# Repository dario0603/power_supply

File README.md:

<p align="left">

</p>

# Linear Power Supply Project

Progetto universitario per la realizzazione e simulazione di un **Alimentatore da Banco Stabilizzato** , completo di schemi elettrici KiCad, simulazioni LTspice, documentazione tecnica e file Gerber per la produzione del PCB.

---

## Panoramica del Progetto

Il progetto riguarda lo studio, la modellizzazione e la progettazione hardware di un alimentatore stabilizzato.

## 1. Obiettivi del Progetto
Il progetto illustra la progettazione di un alimentatore da banco stabilizzato con le seguenti caratteristiche principali:
*   **Tensione di uscita regolabile:** da $0V$ a $20V$ (continua).
*   **Corrente di uscita limitabile e regolabile:** da $0A$ a $5A$.
*   **Modalità Tracking:** permette di erogare in uscita una tensione pari a quella applicata su appositi pin esterni (utile per generare tensioni duali).
*   **Monitoraggio:** Misura in tempo reale di tensione e corrente con visualizzazione a schermo.

## 2. Architettura del Circuito di Potenza
L'alimentatore è strutturato in blocchi funzionali classici:
*   **Trasformatore:** Abbassa la tensione di rete (230V, 50Hz) a un valore di $25V$ efficaci sul secondario.
*   **Raddrizzatore:** È stato scelto un **raddrizzatore a doppia semi-onda** (ponte di diodi) poiché garantisce un fattore di forma migliore e richiede un condensatore di filtro di capacità dimezzata rispetto alla singola semi-onda ($C \approx 14286 \mu F$ per un ripple di $3,5V$).
*   **Filtro Capacitivo:** Livella la tensione raddrizzata riducendo la tensione di ripple.
*   **Regolatore Lineare:** Prende in ingresso la tensione filtrata e la stabilizza al valore desiderato tramite un amplificatore di errore e un transistor di passo.

## 3. Circuito Regolatore e Limitazione di Corrente
Le scelte progettuali più rilevanti per la regolazione e la protezione includono:
*   **Integrato LM723:** Utilizzato come base per il circuito di regolazione della tensione.
*   **Transistor di Potenza (Pass Transistors):** Viene utilizzata una configurazione Darlington per garantire un guadagno di corrente ($\beta_f$) sufficiente. Sono impiegati più transistor di potenza (TIP3055 o 2N3055) **collegati in parallelo** per dividere il carico di corrente.
    *   *Problema critico risolto:* Per evitare il "run-down termico" (squilibrio di corrente dovuto alle variazioni di $\beta_f$ con la temperatura), sono state inserite piccole resistenze di emettitore in serie ai BJT.
*   **Limitatore di Corrente:** Sfrutta una resistenza di shunt ($R_{sh} = 0,2 \Omega$) in serie al carico. La caduta di tensione ai suoi capi è letta da un amplificatore differenziale e confrontata (comparatore) con una tensione di riferimento ($V_{zi}$). Se la corrente supera la soglia, un transistor devia la corrente di base del BJT di passo, limitando l'uscita.

## 4. Alimentazioni Ausiliarie
Per il corretto funzionamento degli amplificatori operazionali (TL082) e della logica di controllo, il circuito ricava tensioni di servizio secondarie:
*   $\pm12V$ stabilizzate (utilizzando LM7812 e LM7912).
*   $+5V$ stabilizzati (tramite LM7805).
*   Tensioni negative specifiche create con diodi Zener per rispettare i limiti di alimentazione degli op-amp nella sezione di tracking in particolare una linea a $-3.8V$.

## 5. Circuiti di Misura (Voltmetro e Amperometro)
Per fornire misurazioni precise all'ADC del microcontrollore (fondo-scala $5V$):
*   **Voltmetro a Guadagno Variabile:** Utilizza un amplificatore non invertente dove il guadagno viene modificato selezionando resistenze di retroazione diverse tramite switch C-MOS analogici (74HC4066). Gestisce fondo-scala di $2V, 10V, 25V, 100V$.
*   **Amperometro con Resistore di Shunt:** Amplifica il segnale prelevato dalla stessa resistenza di shunt della limitazione. Anche qui si usano guadagni variabili per fondo-scala di $200mA, 1A, 2.5A, 8A$.

## 6. Integrità del Segnale e Analisi Termica
*   **Signal Integrity:** È stata calcolata l'induttanza, la capacità e la resistenza parassita delle piste del PCB più critiche. Le simulazioni sul "ringing" hanno confermato che con tempi di salita/discesa $> 5ns$, l'overshoot è trascurabile (sotto il 5%).
*   **Analisi Termica:** Essenziale per i dispositivi di potenza. Analizzando le curve di derating, è stato calcolato il valore di resistenza termica del dissipatore ($R_{thda}$) per i transistor e per il ponte di diodi, evidenziando la necessità (nel caso del TIP3055) di usare la pasta termica e l'eventuale ventilazione forzata per mantenere i componenti sotto le temperature critiche di $125^\circ C / 150^\circ C$.
*   **FMEA (Failure Mode and Effects Analysis):** La relazione contiene tabelle dettagliate per valutare Gravità (S), Occorrenza (O) e Rilevabilità (D) in caso di guasti a condensatori o componenti chiave, calcolando l'indice di rischio globale (RPN).

---

## Simulazioni LTspice

All'interno della directory `Alimentatore taratura manuale/LTspice/` sono presenti due modelli di simulazione (da `v1.0` a `v2.0`):
contenenti varie analisi.

**Analisi di Ripple e Filtraggio**

**Risposta al gradino ($V_{\text{ref}}$)**

**Risposta alla rampa ($V_{\text{ref}}$)**

---

## Progettazione Hardware (KiCad)

I file di progetto PCB e schematici sono realizzati con **KiCad**.

**BOM Interattiva**: Disponibile all'interno delle cartelle KiCad sotto forma di `ibom.html` per facilitare l'assemblaggio dei componenti.

---

## Documentazione e Relazione

Per un'analisi approfondita dei calcoli teorici, delle scelte progettuali e delle prestazioni misurate, fare riferimento alla relazione completa presente nella repository:

* [Relazione Costruzioni (PDF)](Relazione/Relazione%20Costruzioni.pdf)

---

## Struttura della Repository

```text
.
├── Relazione/                        # Documentazione e report tecnico
│   ├── Relazione Costruzioni.pdf     # Documento finale in formato PDF
│   ├── Immagini/                     # Schemi, grafici e diagrammi usati nella relazione
│   └── Simulazioni/                  # File di simulazione generali LTspice
│
├── Alimentatore taratura manuale     # Schemi KiCad e simulazioni LTspice
│   ├── LtSpice
│   └── KiCad      
└── Controllore taratura manuale      # Schemi del controllore manuale

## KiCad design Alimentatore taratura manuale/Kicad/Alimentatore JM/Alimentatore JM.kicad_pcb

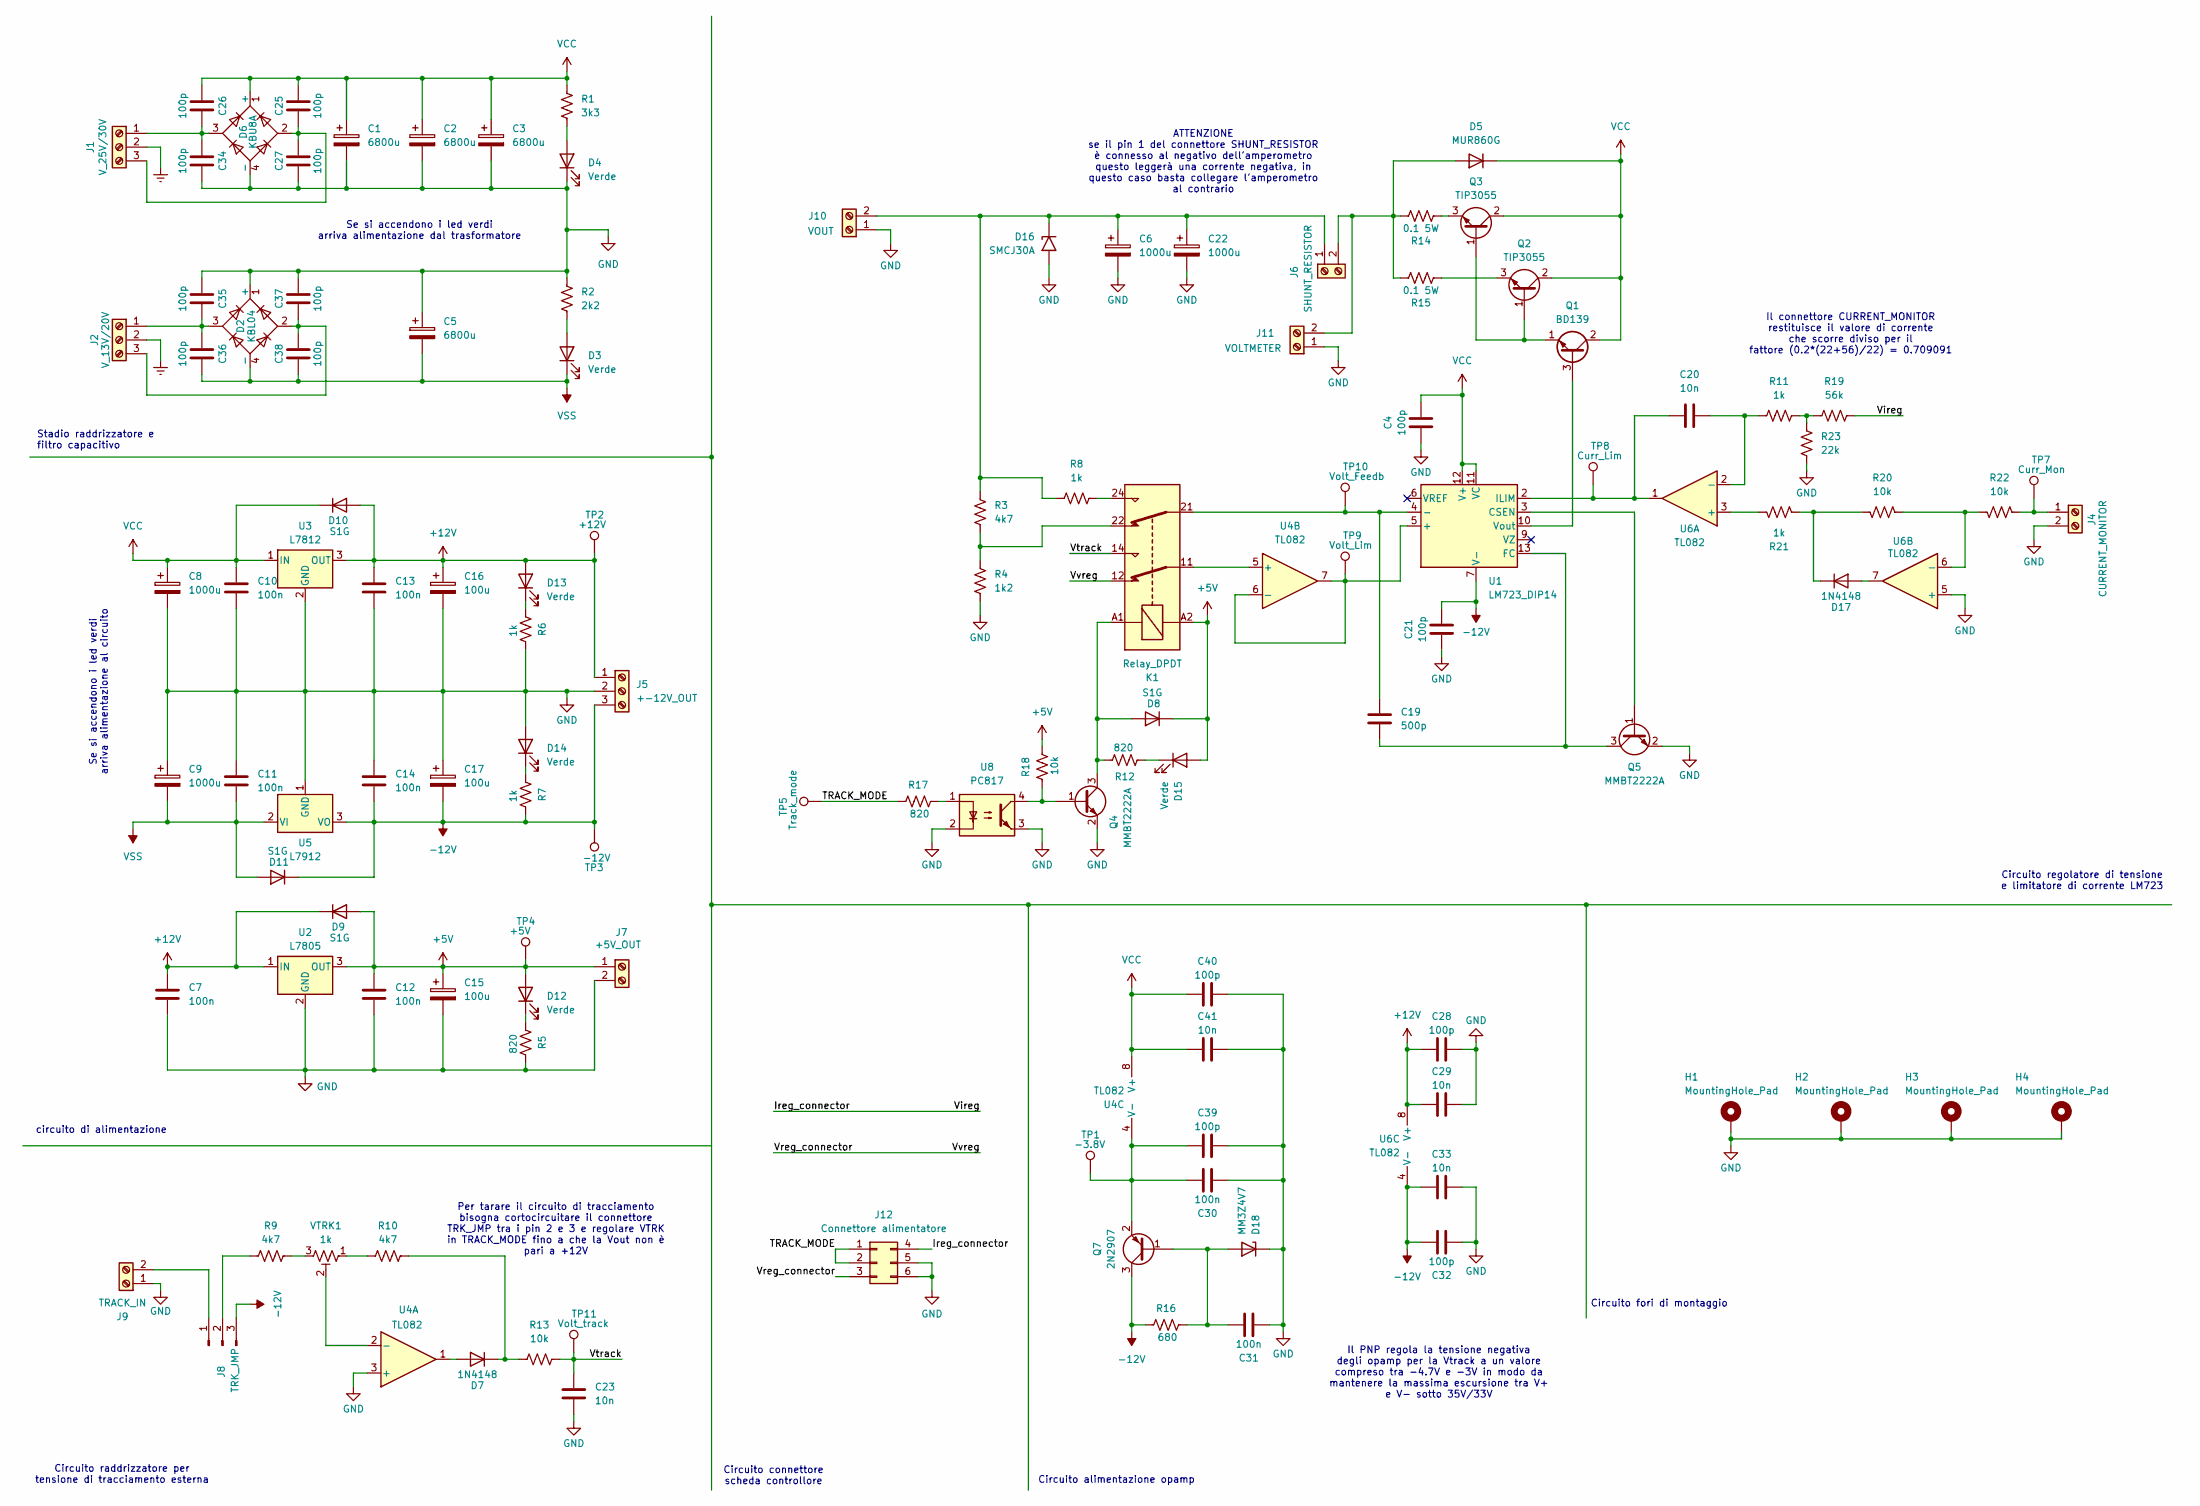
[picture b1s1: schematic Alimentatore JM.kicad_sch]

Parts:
C1, C2, C3, C5: 6800u; CP_Radial_D18.0mm_P7.50mm
C4, C21, C25, C26, C27, C28, C32, C34, C35, C36, C37, C38, C39, C40: 100p; C_0805_2012Metric_Pad1.18x1.45mm_HandSolder
C6, C8, C9, C22: 1000u; CP_Elec_8x10.5
C7, C10, C11, C12, C13, C14, C30, C31: 100n; C_0805_2012Metric_Pad1.18x1.45mm_HandSolder
C15, C16, C17: 100u; CP_Elec_8x10.5
C19: 500p; C_0805_2012Metric_Pad1.18x1.45mm_HandSolder
C20, C23, C29, C33, C41: 10n; C_0805_2012Metric_Pad1.18x1.45mm_HandSolder
D2: KBL04; Diode_Bridge_Vishay_KBL
D3, D4, D12, D13, D14, D15: Verde; LED_0805_2012Metric_Pad1.15x1.40mm_HandSolder
D5: MUR860G; TO-220-2_Vertical
D6: KBU8A; Diode_Bridge_Vishay_KBU
D7, D17: 1N4148; D_SOD-323F
D8, D9, D10, D11: S1G; D_SMA_Handsoldering
D16: SMCJ30A; D_SMC_Handsoldering
D18: MM3Z4V7; D_DO-35_SOD27_P7.62mm_Horizontal
H1, H2, H3, H4: MountingHole_Pad; MountingHole_3.2mm_M3_DIN965_Pad
J1: V_25V/30V; TerminalBlock_Phoenix_MKDS-1,5-3-5.08_1x03_P5.08mm_Horizont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
J2: V_13V/20V; TerminalBlock_Phoenix_MKDS-1,5-3-5.08_1x03_P5.08mm_Horizont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
J4: CURRENT_MONITOR; TerminalBlock_Phoenix_MKDS-1,5-2-5.08_1x02_P5.08mm_Horizont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
J5: +-12V_OUT; TerminalBlock_Phoenix_MKDS-1,5-3-5.08_1x03_P5.08mm_Horizont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
J6: SHUNT_RESISTOR; TerminalBlock_Phoenix_MKDS-1,5-2-5.08_1x02_P5.08mm_Horizont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
J7: +5V_OUT; TerminalBlock_Phoenix_MKDS-1,5-2-5.08_1x02_P5.08mm_Horizont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
J8: TRK_JMP; PinHeader_1x03_P2.54mm_Vertical
J9: TRACK_IN; TerminalBlock_Phoenix_MKDS-1,5-2-5.08_1x02_P5.08mm_Horizont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
J10: VOUT; TerminalBlock_Phoenix_MKDS-1,5-2-5.08_1x02_P5.08mm_Horizont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
J11: VOLTMETER; TerminalBlock_Phoenix_MKDS-1,5-2-5.08_1x02_P5.08mm_Horizont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
J12: Connettore alimentatore; PinHeader_2x03_P2.54mm_Vertical
K1: Relay_DPDT; Relay_DPDT_Finder_30.22
Q1: BD139; TO-126-3_Vertical
Q2, Q3: TIP3055; TO-218-3_Vertical
Q4, Q5: MMBT2222A; SOT-23
Q7: 2N2907; SOT-23
R1: 3k3; R_0805_2012Metric_Pad1.20x1.40mm_HandSolder
R2: 2k2; R_0805_2012Metric_Pad1.20x1.40mm_HandSolder
R3, R9, R10: 4k7; R_0805_2012Metric_Pad1.20x1.40mm_HandSolder
R4: 1k2; R_0805_2012Metric_Pad1.20x1.40mm_HandSolder
R5, R12, R17: 820; R_0805_2012Metric_Pad1.20x1.40mm_HandSolder
R6, R7, R8, R11, R21: 1k; R_0805_2012Metric_Pad1.20x1.40mm_HandSolder
R13, R18, R20, R22: 10k; R_0805_2012Metric_Pad1.20x1.40mm_HandSolder
R14, R15: 0.1 5W; R_Box_L14.0mm_W5.0mm_P9.00mm
R16: 680; R_0805_2012Metric_Pad1.20x1.40mm_HandSolder
R19: 56k; R_0805_2012Metric_Pad1.20x1.40mm_HandSolder
R23: 22k; R_0805_2012Metric_Pad1.20x1.40mm_HandSolder
TP1: -3.8V; TestPoint_Pad_D1.0mm
TP2: +12V; TestPoint_Pad_D1.0mm
TP3: -12V; TestPoint_Pad_D1.0mm
TP4: +5V; TestPoint_Pad_D1.0mm
TP5: Track_mode; TestPoint_Pad_D1.0mm
TP7: Curr_Mon; TestPoint_Pad_D1.0mm
TP8: Curr_Lim; TestPoint_Pad_D1.0mm
TP9: Volt_Lim; TestPoint_Pad_D1.0mm
TP10: Volt_Feedb; TestPoint_Pad_D1.0mm
TP11: Volt_track; TestPoint_Pad_D1.0mm
U1: LM723_DIP14; DIP-14_W7.62mm_LongPads
U2: L7805; TO-252-2
U3: L7812; TO-263-2
U4, U6: TL082; SOIC-8_3.9x4.9mm_P1.27mm
U5: L7912; TO-263-2
U8: PC817; DIP-4_W7.62mm_LongPads
VTRK1: 1k; Potentiometer_Runtron_RM-065_Vertical

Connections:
+5V: C12.1, C15.1, D8.1 (K), D9.2 (A), D12.2 (A), D15.2 (A), J7.1, K1.A2, R18.2, TP4.1, U2.3 (OUT)
+12V: C7.1, C13.1, C16.1, C28.1, C29.1, D9.1 (K), D10.2 (A), D13.2 (A), J5.1, TP2.1, U2.1 (IN), U3.3 (OUT), U6.8 (V+)
-12V: C14.2, C17.2, C21.2, C32.2, C33.1, D11.1 (K), J5.3, J8.3, Q7.3 (C), R7.2, R16.1, TP3.1, U1.7 (V-), U5.3 (VO), U6.4 (V-)
/Ireg_connector: J12.4, R19.2
/TRACK_MODE: J12.1, J12.2, R17.1, TP5.1
/Vreg_connector: J12.3, K1.12
/Vtrack: C23.1, K1.14, R13.2, TP11.1
Earth: J1.2, J2.2
GND: C1.2, C2.2, C3.2, C4.1, C5.1, C6.2, C7.2, C8.2, C9.1, C10.2, C11.1, C12.2, C13.2, C14.1, C15.2, C16.2, C17.1, C21.1, C22.2, C23.2, C27.1, C28.2, C29.2, C30.1, C31.1, C32.1, C33.2, C34.1, C35.2, C37.2, C39.2, C40.2, C41.2, D2.1 (+), D4.1 (K), D6.4 (-), D14.2 (A), D16.2 (A2), D18.1 (K), H1.1, H2.1, H3.1, H4.1, J4.2, J5.2, J7.2, J9.1, J10.1, J11.1, J12.5, J12.6, Q4.2 (E), Q5.2 (E), R2.1, R4.2, R5.2, R6.2, R23.1, U2.2 (GND), U3.2 (GND), U4.3 (+), U5.1 (GND), U6.5 (+), U8.2, U8.3
unnamed: D3.2 (A), R2.2
unnamed: D4.2 (A), R1.2
unnamed: D5.2 (A), J6.2, J11.2, R14.2, R15.2
unnamed: D7.2 (A), U4.1
unnamed: D7.1 (K), R10.2, R13.1
unnamed: D8.2 (A), K1.A1, Q4.3 (C), R12.2
unnamed: D12.1 (K), R5.1
unnamed: D13.1 (K), R6.1
unnamed: D14.1 (K), R7.1
unnamed: D15.1 (K), R12.1
unnamed: C6.1, C22.1, D16.1 (A1), J6.1, J10.2, R3.1, R8.1
unnamed: D17.2 (A), U6.7
unnamed: D17.1 (K), R20.2, R21.1
unnamed: C31.2, D18.2 (A), Q7.1 (B), R16.2
unnamed: C26.1, C34.2, D6.3, J1.1
unnamed: C25.1, C27.2, D6.2, J1.3
unnamed: C35.1, C36.2, D2.3, J2.1
unnamed: C37.1, C38.2, D2.2, J2.3
unnamed: J4.1, R22.1, TP7.1
unnamed: J8.1, J9.2
unnamed: J8.2, R9.1
unnamed: K1.22, R3.2, R4.1
unnamed: K1.24, R8.2
unnamed: Q1.3 (B), U1.10 (Vout)
unnamed: Q1.1 (E), Q2.1 (B), Q3.1 (B)
unnamed: Q2.3 (E), R15.1
unnamed: Q3.3 (E), R14.1
unnamed: Q4.1 (B), R18.1, U8.4
unnamed: Q5.1 (B), U1.3 (CSEN)
unnamed: C19.2, Q5.3 (C), U1.13 (FC)
unnamed: C30.2, C39.1, Q7.2 (E), TP1.1, U4.4 (V-)
unnamed: R9.2, VTRK1.3
unnamed: R10.1, VTRK1.1
unnamed: R11.2, R19.1, R23.2
unnamed: R17.2, U8.1
unnamed: TP9.1, U1.5 (+), U4.6 (-), U4.7
unnamed: C19.1, K1.21, TP10.1, U1.4 (-)
unnamed: C20.1, TP8.1, U1.2 (ILIM), U6.1
unnamed: U4.2 (-), VTRK1.2
unnamed: K1.11, U4.5 (+)
unnamed: R21.2, U6.3 (+)
unnamed: C20.2, R11.1, U6.2 (-)
unnamed: R20.1, R22.2, U6.6 (-)
VCC: C1.1, C2.1, C3.1, C4.2, C8.1, C10.1, C25.2, C26.2, C40.1, C41.1, D5.1 (K), D6.1 (+), D10.1 (K), Q1.2 (C), Q2.2 (C), Q3.2 (C), R1.1, U1.11 (VC), U1.12 (V+), U3.1 (IN), U4.8 (V+)
VSS: C5.2, C9.2, C11.2, C36.1, C38.1, D2.4 (-), D3.1 (K), D11.2 (A), U5.2 (VI)

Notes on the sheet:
Per tarare il circuito di tracciamento bisogna cortocircuitare il connettore TRK_JMP tra i pin 2 e 3 e regolare VTRK in TRACK_MODE fino a che la Vout non è pari a +12V
circuito di alimentazione
Circuito connettore scheda controllore
Circuito fori di montaggio
Stadio raddrizzatore e filtro capacitivo
Circuito alimentazione opamp
Se si accendono i led verdi arriva alimentazione dal trasformatore
Circuito regolatore di tensione e limitatore di corrente LM723
Il connettore CURRENT_MONITOR restituisce il valore di corrente che scorre diviso per il fattore (0.2*(22+56)/22) = 0.709091
Il PNP regola la tensione negativa degli opamp per la Vtrack a un valore compreso tra -4.7V e -3V in modo da mantenere la massima escursione tra V+ e V- sotto 35V/33V
Se si accendono i led verdi arriva alimentazione al circuito
Circuito raddrizzatore per tensione di tracciamento esterna
ATTENZIONE se il pin 1 del connettore SHUNT_RESISTOR è connesso al negativo dell'amperometro questo leggerà una corrente negativa, in questo caso basta collegare l'amperometro al contrario

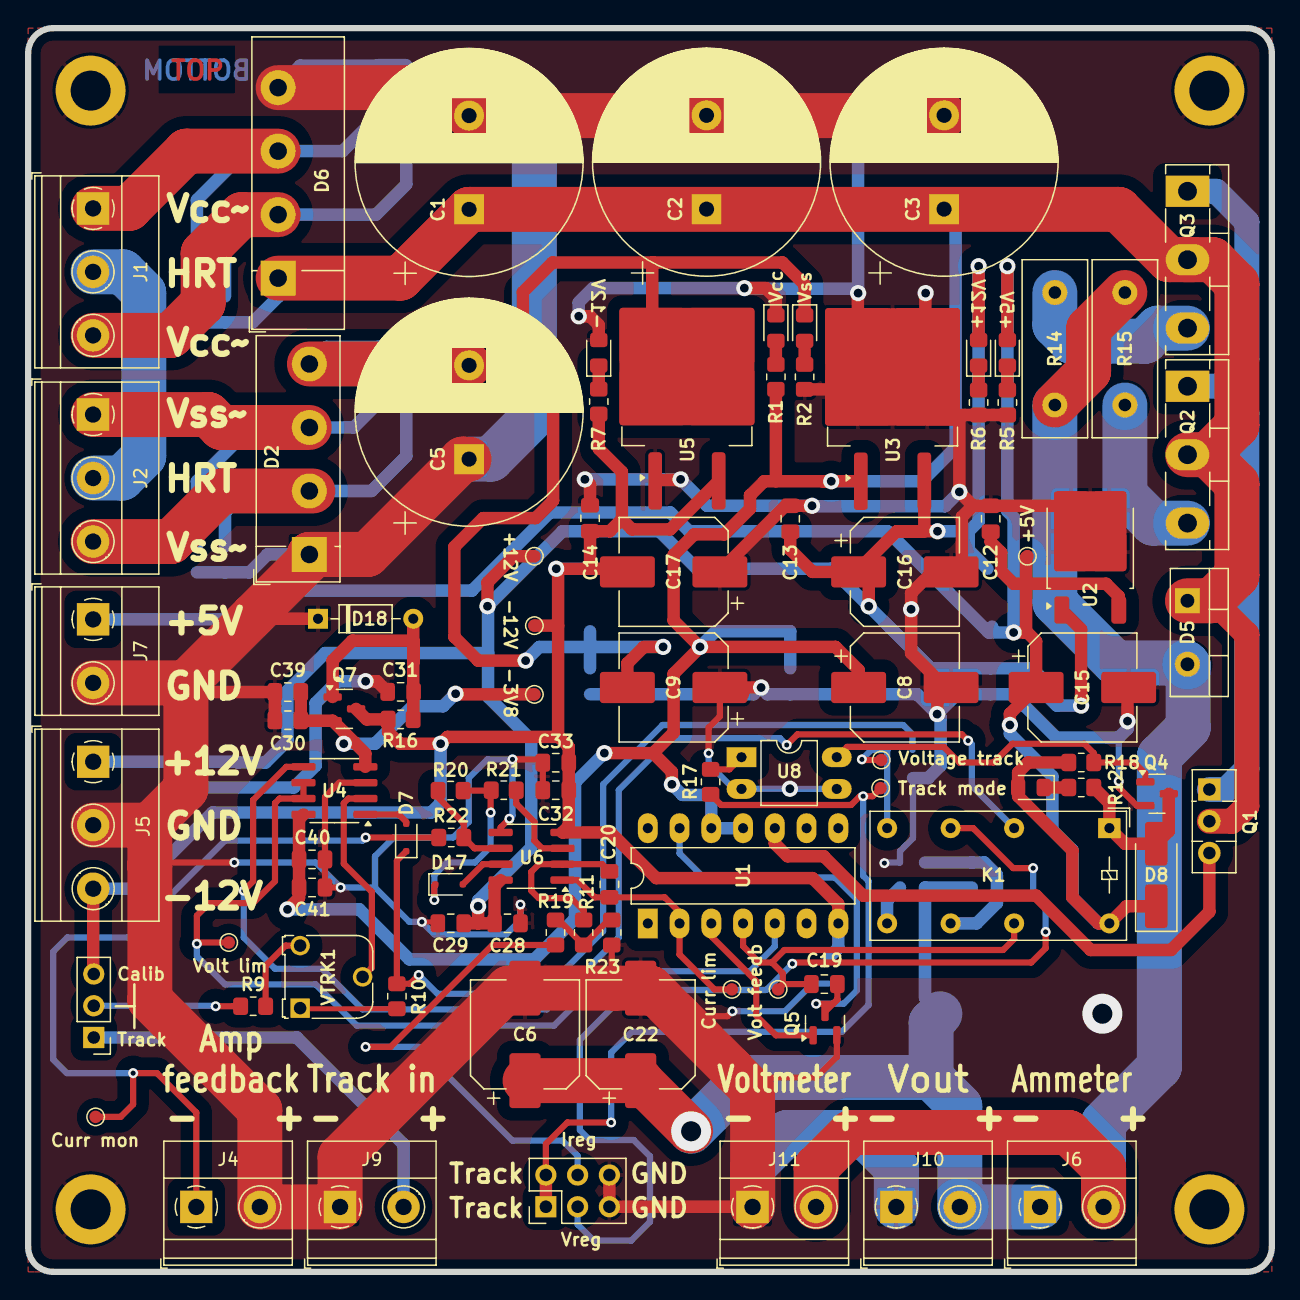
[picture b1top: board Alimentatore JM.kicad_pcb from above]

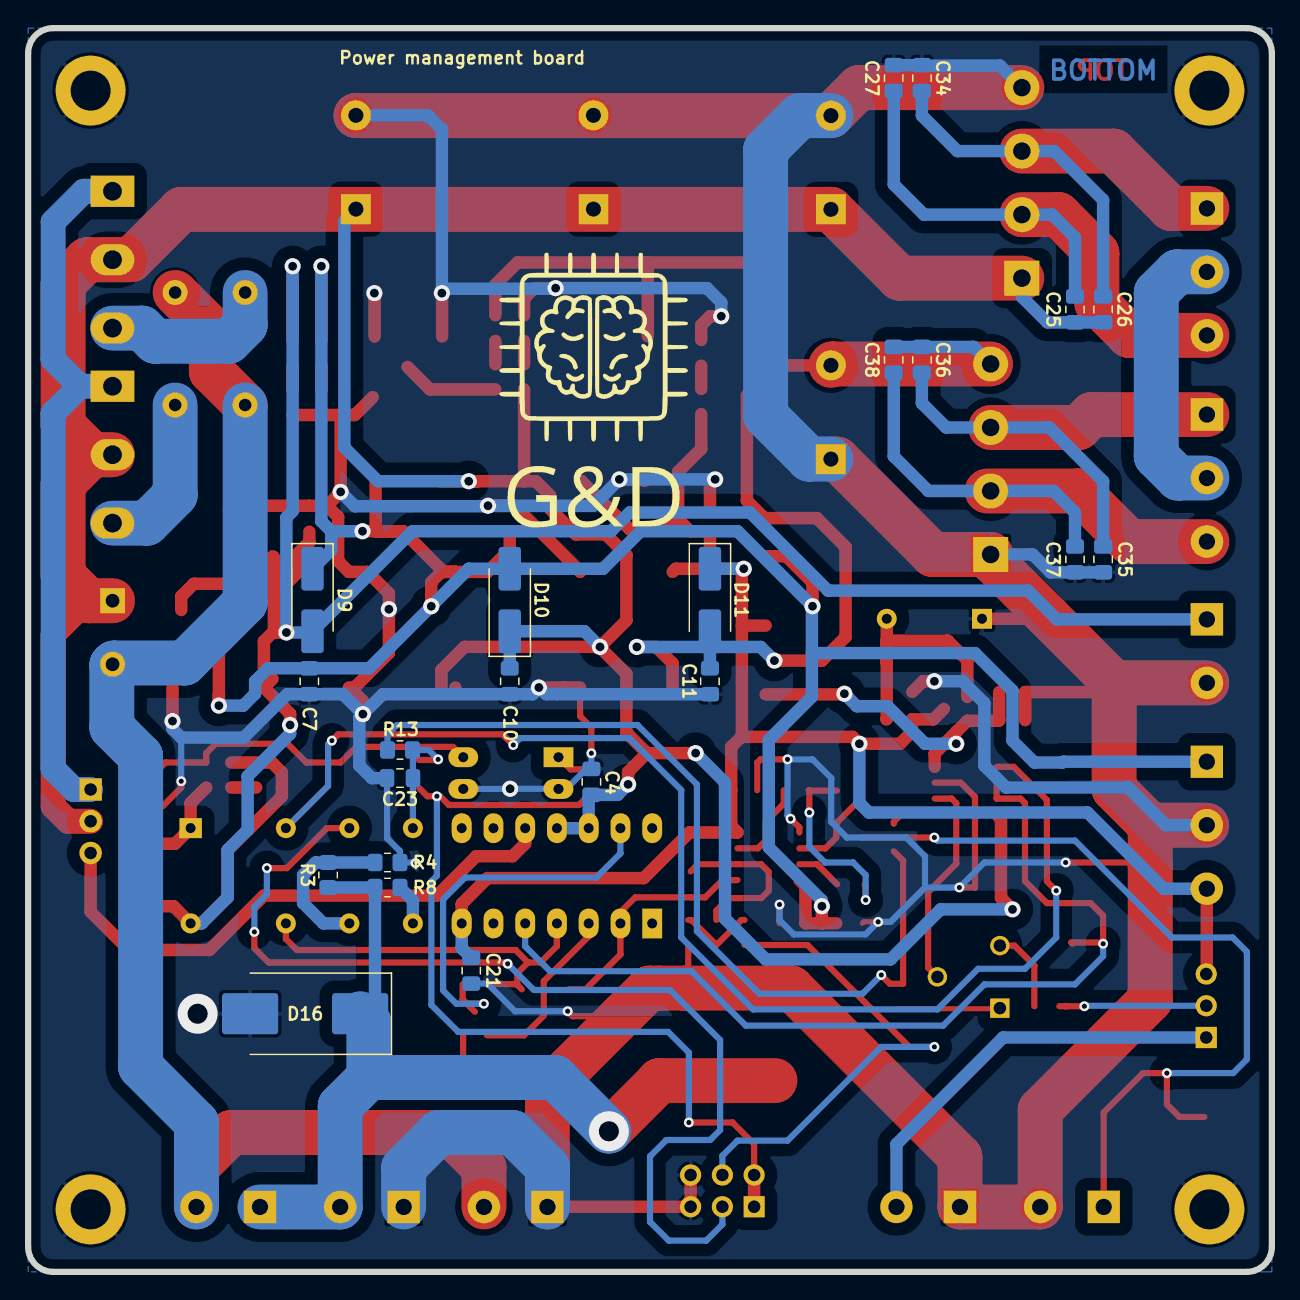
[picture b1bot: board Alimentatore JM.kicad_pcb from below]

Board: 2 copper layers, 99.5 x 99.5 mm, 119 parts (22 on the bottom side), 54 nets.
